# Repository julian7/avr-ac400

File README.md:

# Record Power AC400 controller

This repository contains a drop-in replacement PCB and firmware for the [Record Power AC400 Air Filter controller](https://www.recordpower.co.uk/product/two-stage-air-filter-with-remote-3-speeds-and-time-delay).

The original AC400 controller is prone to failure due to its simplistic power supply design, which often results in various failures. While the company's support is very good, the replacement controller is still prone to the same issues.

This design aims to provide a solution that is more robust, and tries to keep using original parts where possible. It also uses an ~~ATmega88PA~~ ATmega328P microcontroller, as existing refurbishment stock (note: the ATmega88 I had probably has SPIEN fuse unprogrammed, so I couldn't flash it at the end). The PCB and firmware is compatible with the whole line of ATmega48P/88P/168PA/328P line though.

## Case design

The board PCB is designed to fit into the original AC400 electronics enclosure, but there is a different LED divider grill design, which is 3D printed. The 3D model and the FreeCAD source are available in the `mechanical` directory, and it can be printed with a 3D printer.

The 3D design and model for the case is also provided, to allow further modifications.

## PCB design

The PCB is designed using KiCad 10, and is available in the `hardware` directory. The form factor is designed to fit into the original AC400 enclosure, and it uses the same connectors for the fan and power supply. It relies of the Alternative Kicad Library plugin for resistor footprints. Interactive BOM is generated using the [Interactive Html Bom](Github: https://github.com/openscopeproject/InteractiveHtmlBom) plugin, and gerber file packages are generated using the [gerber to order](https://github.com/asukiaaa/gerber_to_order) plugin.

## Firmware

The firmware is written in C using AVR-GCC toolchain, and it is available in the `firmware` directory. It is based on the original firmware functionality, with some improvements and bug fixes.

## Flashing the firmware

To flash the firmware onto the microcontroller, you will need an AVR programmer (e.g., USBasp, [ATMEL-ICE](https://www.microchip.com/en-us/development-tool/atatmel-ice)) and AVRDUDE software.

## Measurement points and troubleshooting

The PCB includes test points for measuring various signals:

- TP1: 3.3V power supply
- TP2: Ground
- TP3: Low speed mosfet drain
- TP4: Low speed mosfet gate
- TP5: Mid speed mosfet drain
- TP6: Mid speed mosfet gate
- TP7: High speed mosfet drain
- TP8: High speed mosfet gate

When troubleshooting, supply 3.3V power to the PCB through J8, so that 230V is not present on the board.

J1 is providing standard ISP connectivity. Manual reset can be performed by shorting JP1 (also labeled "RESET").

## Wiring and functions

When assembled into the original AC400 enclosure, the PCB will be connected to the following components:

- LINE IN: 230V AC input
- COMMON IN: Common line for the fan and the power supply
- COMMON OUT: White wire to the fan
- LOW OUT: Blue (or brown) wire to the fan
- MID OUT: Black wire to the fan
- HIGH OUT: Red wire to the fan

LED functions:

- LED1: Timer for 1 hour
- LED2: Timer for 2 hours
- LED3: Timer for 4 hours
- LED4: High speed indicator
- LED5: Medium speed indicator
- LED6: Low speed indicator

Button functions:

- SW1: On/Speed (cycles through Off, Low, Mid, High)
- SW2: Off

Infrared remote control functions:

- Red: Off
- Green: On/Speed
- Yellow: Timer (cycles through Off, 1 hour, 2 hours, 4 hours)

Buzzer signals:

- Short beep: Button press / infrared button feedback
- Long beep: Timer end
- Long beep with 1/2/4 short beeps: timer set to 1/2/4 hours
- Two long beeps: Off

## Build experience

Building this project was quite an experience. First off, soldering the MCU was not much of a challenge, and I felt like I could handle 0603 package size too, or even 0402 if the space is tight. I would use an ESP32-C3 board if I were to do it again: that would make it remote controllable.

Originally, I wanted to use an old ATmega88PA, but I couldn't even read its fuses. So that I ordered a few ATmega328P, which are pin-compatible. Fortunately, because I could made one of them a short circuit. It would've been nicer if the design accepted ATmega328PB, but I just didn't want to risk cutting wires at that point.

I almost fried my Raspberry Pi4 while writing the firmware, so buying a very cheap USBASP now feels like a no brainer. It's also not that bad if you don't screw up the ISP pinout. Fortunately, I could patch it up with bodge wires. Also, there was a nasty case of weird behavior and browning out, but as it turns out that was just microzig acting up. Switching back to avr-libc made the issue go away.

The original plan was to reuse the original case and the 12mm TACT switches, but I mistakenly ordered an earlier version of the PCB, where mounting holes have been placed closer together so I ended up 3D printing my own case. Later on, I even managed to break off the buttons as I tried to assemble it back together, and I only had 6x6mm switches so I ended up propping up some button spacers to be able to operate the device.

All in all, I'm very happy about the outcome.  Obviously it could've been much better, but this is still well beyond my expectations.

## Similar projects

- [AC400Controller](https://github.com/thikone/AC400Controller): drop-in replacement PCB, firmware, and 3D printed enclosure. It uses Arduino Nano as the controller.

## License

This project is licensed under the Creative Commons Attribution 4.0 International License. See the [LICENSE](./LICENSE.md) file for details.

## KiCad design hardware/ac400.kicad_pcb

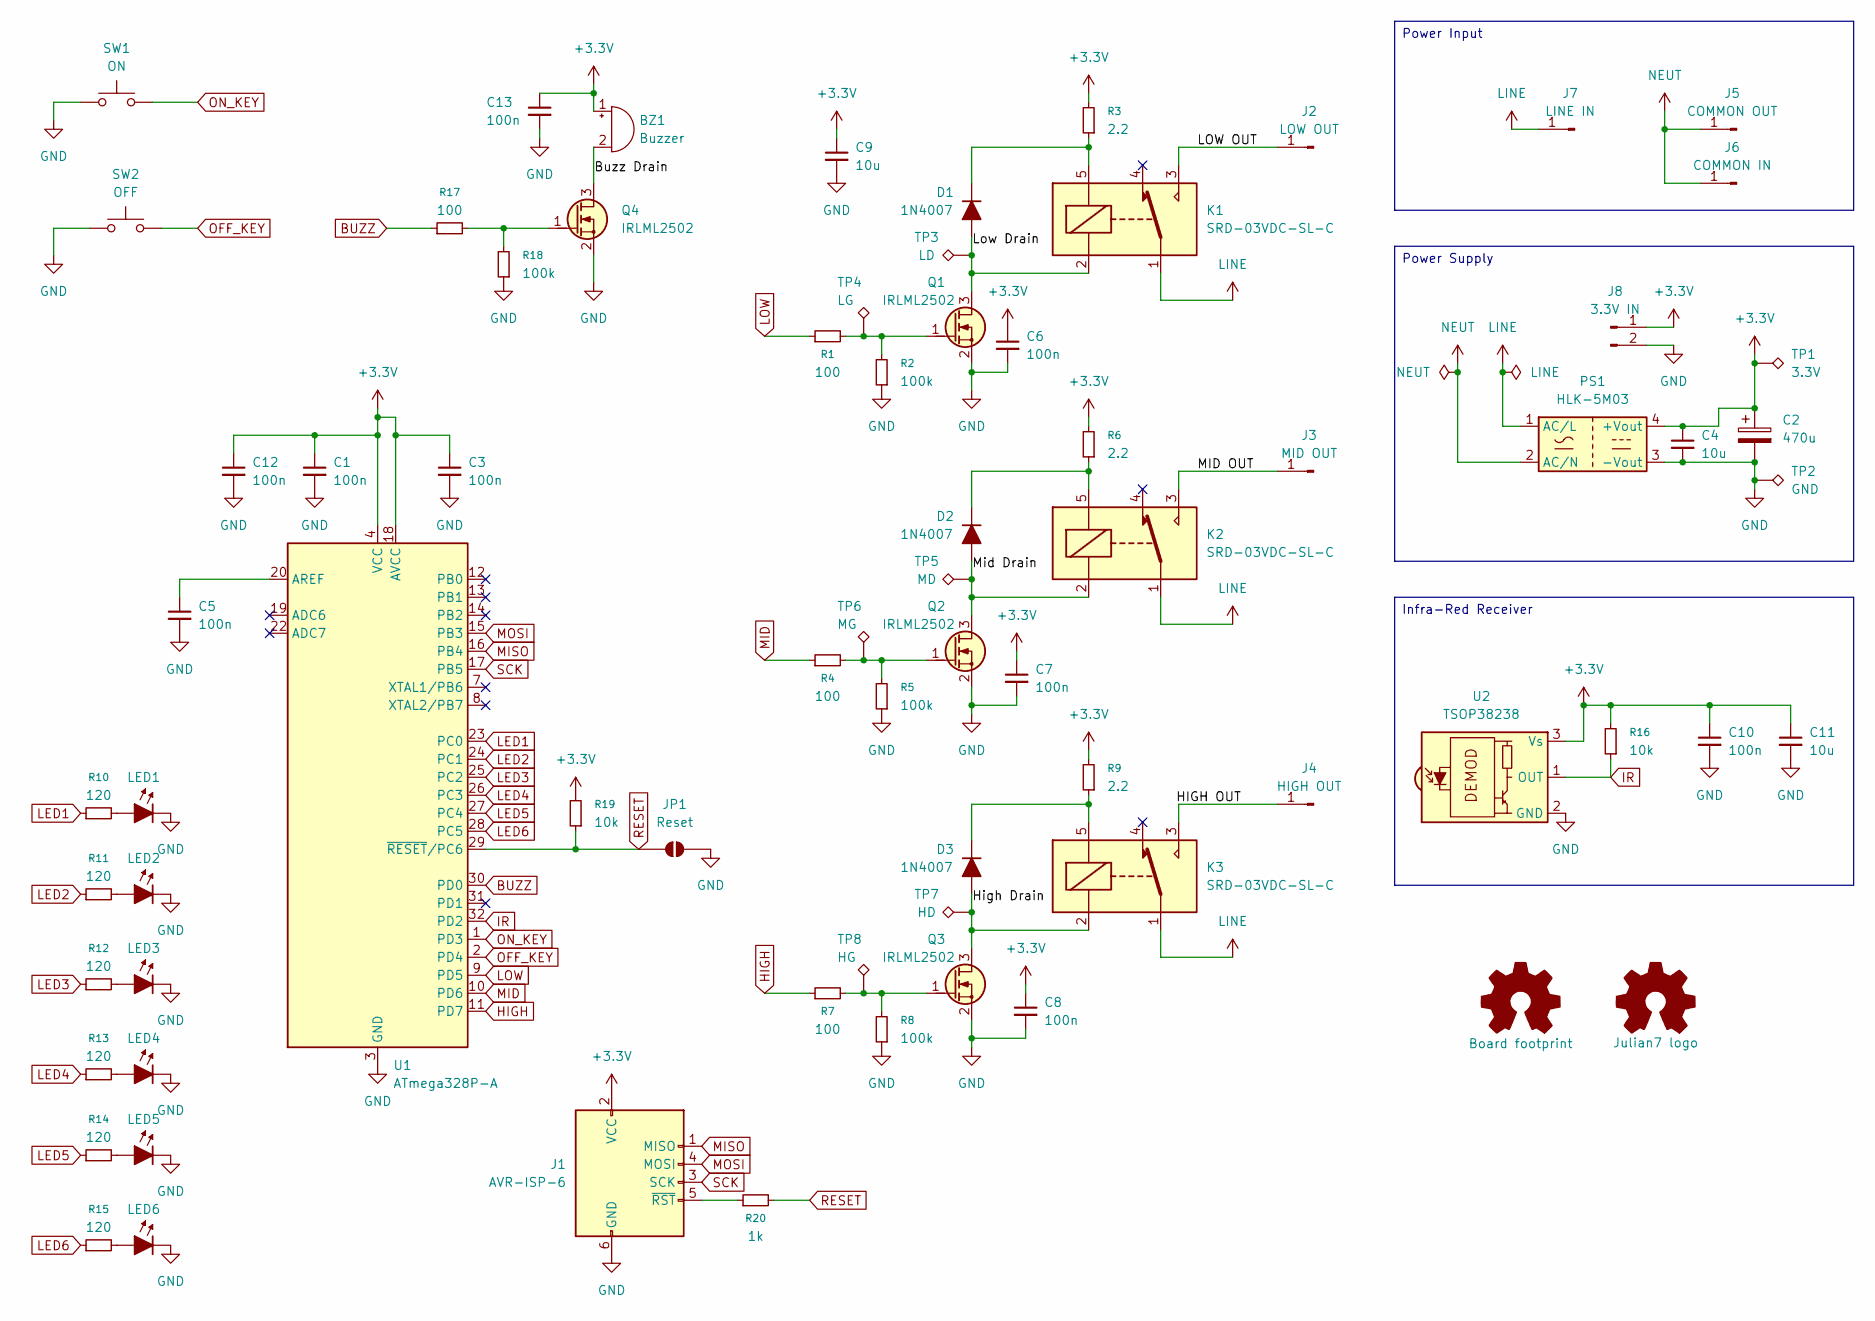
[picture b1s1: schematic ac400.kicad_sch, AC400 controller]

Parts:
BZ1: Buzzer; Buzzer_12x9.5RM7.6
C1, C3, C5, C6, C7, C8, C10, C12, C13: 100n; C_0805_2012Metric_Pad1.18x1.45mm_HandSolder
C2: 470u; CP_Radial_D8.0mm_P3.50mm
C4, C9, C11: 10u; C_0805_2012Metric_Pad1.18x1.45mm_HandSolder
D1, D2, D3: 1N4007; D_SOD-323
J1: AVR-ISP-6; IDC-Header_2x03_P2.54mm_Vertical
J2: LOW OUT; SolderWire-1.5sqmm_1x01_D1.7mm_OD3.9mm
J3: MID OUT; SolderWire-1.5sqmm_1x01_D1.7mm_OD3.9mm
J4: HIGH OUT; SolderWire-1.5sqmm_1x01_D1.7mm_OD3.9mm
J5: COMMON OUT; SolderWire-1.5sqmm_1x01_D1.7mm_OD3.9mm
J6: COMMON IN; SolderWire-1.5sqmm_1x01_D1.7mm_OD3.9mm
J7: LINE IN; SolderWire-1.5sqmm_1x01_D1.7mm_OD3.9mm
J8: 3.3V IN; PinHeader_1x02_P2.54mm_Vertical
JP1: Reset; SolderJumper-2_P1.3mm_Open_TrianglePad1.0x1.5mm
K1, K2, K3: SRD-03VDC-SL-C; Relay_SPDT_SANYOU_SRD_Series_Form_C
LED1, LED2, LED3, LED4, LED5, LED6: OF-SMD 2012 Green; LED_0805_2012Metric
PS1: HLK-5M03; Converter_ACDC_Hi-Link_HLK-5Mxx
Q1, Q2, Q3, Q4: IRLML2502; SOT-23
R1, R4, R7, R17: 100; R_0805_2012Metric_Pad1.15x1.40mm_HandSolder
R2, R5, R8, R18: 100k; R_0805_2012Metric_Pad1.15x1.40mm_HandSolder
R3, R6, R9: 2.2; R_0805_2012Metric_Pad1.15x1.40mm_HandSolder
R10, R11, R12, R13, R14, R15: 120; R_0805_2012Metric_Pad1.15x1.40mm_HandSolder
R16, R19: 10k; R_0805_2012Metric_Pad1.15x1.40mm_HandSolder
R20: 1k; R_0805_2012Metric_Pad1.15x1.40mm_HandSolder
SW1: ON; SW_PUSH-12mm
SW2: OFF; SW_PUSH-12mm
SYM1: Board footprint; board_shape
SYM2: Julian7 logo; julian7_makers_mark
TP1: 3.3V; TestPoint_Pad_D2.0mm
TP2: GND; TestPoint_Pad_2.0x2.0mm
TP3: LD; TestPoint_Pad_D2.0mm
TP4: LG; TestPoint_Pad_D2.0mm
TP5: MD; TestPoint_Pad_D2.0mm
TP6: MG; TestPoint_Pad_D2.0mm
TP7: HD; TestPoint_Pad_D2.0mm
TP8: HG; TestPoint_Pad_D2.0mm
U1: ATmega328P-A; TQFP-32_7x7mm_P0.8mm
U2: TSOP38238; Vishay_MINICAST-3Pin

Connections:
+3.3V: BZ1.1 (+), C1.1, C2.1, C3.1, C4.1, C6.1, C7.1, C8.1, C9.1, C10.1, C11.1, C12.1, C13.1, J1.2 (VCC), J8.1, PS1.4 (+Vout), R3.2, R6.2, R9.2, R16.2, R19.2, TP1.1 (1_1), U1.4 (VCC), U1.6 (VCC), U1.18 (AVCC), U2.3 (Vs)
/Buzz Drain: BZ1.2 (-), Q4.3 (D)
/HIGH OUT: J4.1 (Pin_1_1), K3.3
/High Drain: D3.2 (A), K3.2, Q3.3 (D), TP7.1 (1_1)
/LOW OUT: J2.1 (Pin_1_1), K1.3
/Low Drain: D1.2 (A), K1.2, Q1.3 (D), TP3.1 (1_1)
/MID OUT: J3.1 (Pin_1_1), K2.3
/Mid Drain: D2.2 (A), K2.2, Q2.3 (D), TP5.1 (1_1)
BUZZ: R17.1, U1.30 (PD0)
GND: C1.2, C2.2, C3.2, C4.2, C5.2, C6.2, C7.2, C8.2, C9.2, C10.2, C11.2, C12.2, C13.2, J1.6 (GND), J8.2, JP1.2 (B), LED1.1 (K), LED2.1 (K), LED3.1 (K), LED4.1 (K), LED5.1 (K), LED6.1 (K), PS1.3 (-Vout), Q1.2 (S), Q2.2 (S), Q3.2 (S), Q4.2 (S), R2.1, R5.1, R8.1, R18.1, SW1.1, SW2.1, TP2.1 (1_1), U1.3 (GND), U1.5 (GND), U1.21 (GND), U2.2 (GND)
HIGH: R7.1, U1.11 (PD7)
IR: R16.1, U1.32 (PD2), U2.1 (OUT)
LED1: R10.1, U1.23 (PC0)
LED2: R11.1, U1.24 (PC1)
LED3: R12.1, U1.25 (PC2)
LED4: R13.1, U1.26 (PC3)
LED5: R14.1, U1.27 (PC4)
LED6: R15.1, U1.28 (PC5)
LINE: J7.1 (Pin_1_1), K1.1, K2.1, K3.1, PS1.1 (AC/L)
LOW: R1.1, U1.9 (PD5)
MID: R4.1, U1.10 (PD6)
MISO: J1.1 (MISO), U1.16 (PB4)
MOSI: J1.4 (MOSI), U1.15 (PB3)
NEUT: J5.1 (Pin_1_1), J6.1 (Pin_1_1), PS1.2 (AC/N)
unnamed: D1.1 (K), K1.5, R3.1
unnamed: D2.1 (K), K2.5, R6.1
unnamed: D3.1 (K), K3.5, R9.1
unnamed: J1.5 (~RST), R20.1
unnamed: LED1.2 (A), R10.2
unnamed: LED2.2 (A), R11.2
unnamed: LED3.2 (A), R12.2
unnamed: LED4.2 (A), R13.2
unnamed: LED5.2 (A), R14.2
unnamed: LED6.2 (A), R15.2
unnamed: Q1.1 (G), R1.2, R2.2, TP4.1 (1_1)
unnamed: Q2.1 (G), R4.2, R5.2, TP6.1 (1_1)
unnamed: Q3.1 (G), R7.2, R8.2, TP8.1 (1_1)
unnamed: Q4.1 (G), R17.2, R18.2
unnamed: C5.1, U1.20 (AREF)
OFF_KEY: SW2.2, U1.2 (PD4)
ON_KEY: SW1.2, U1.1 (PD3)
RESET: JP1.1 (A), R19.1, R20.2, U1.29 (~RESET/PC6)
SCK: J1.3 (SCK), U1.17 (PB5)

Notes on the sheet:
Power Input
Power Supply
Infra-Red Receiver

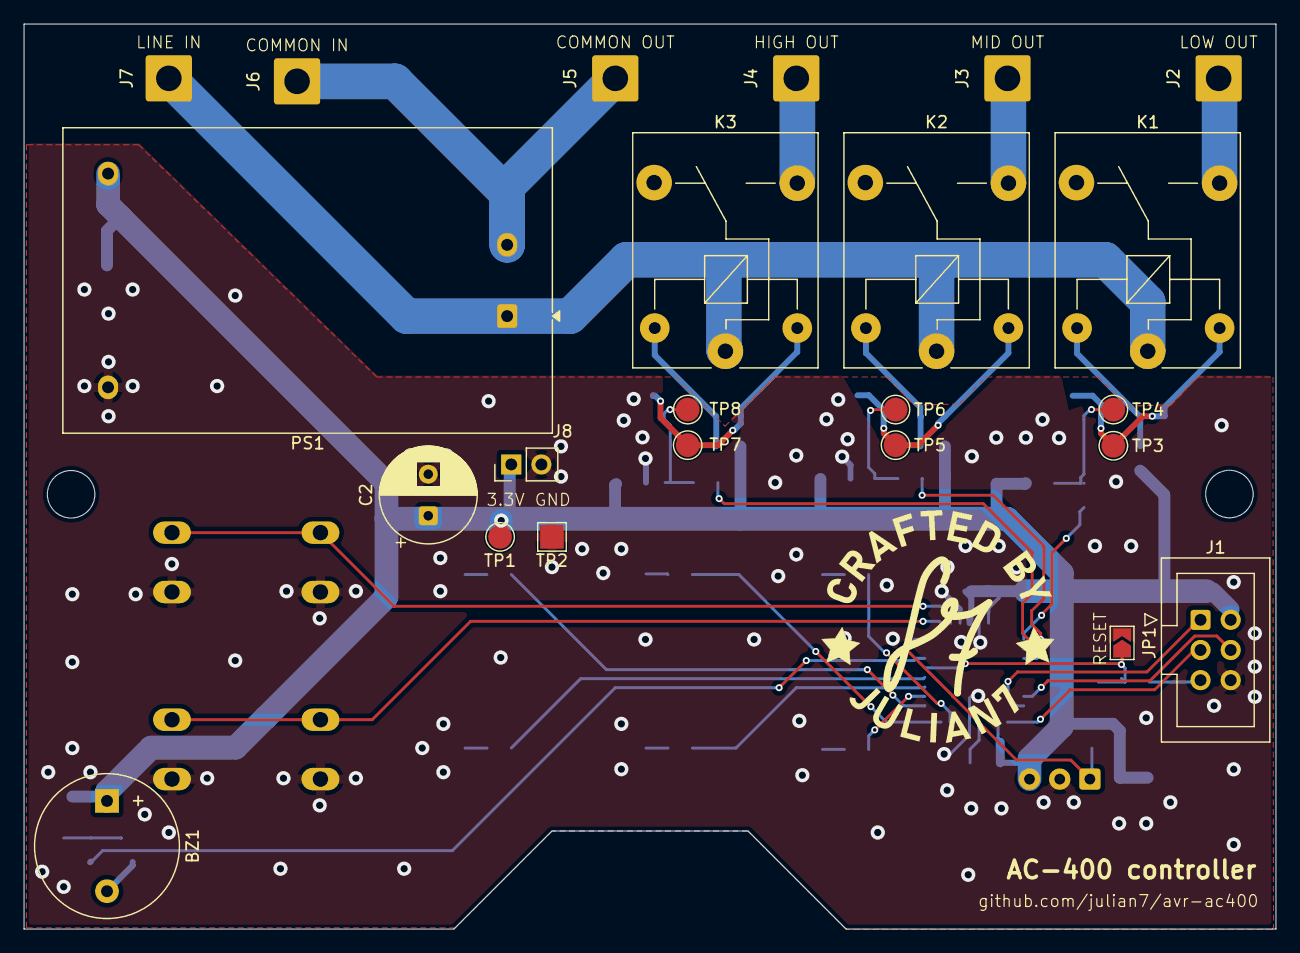
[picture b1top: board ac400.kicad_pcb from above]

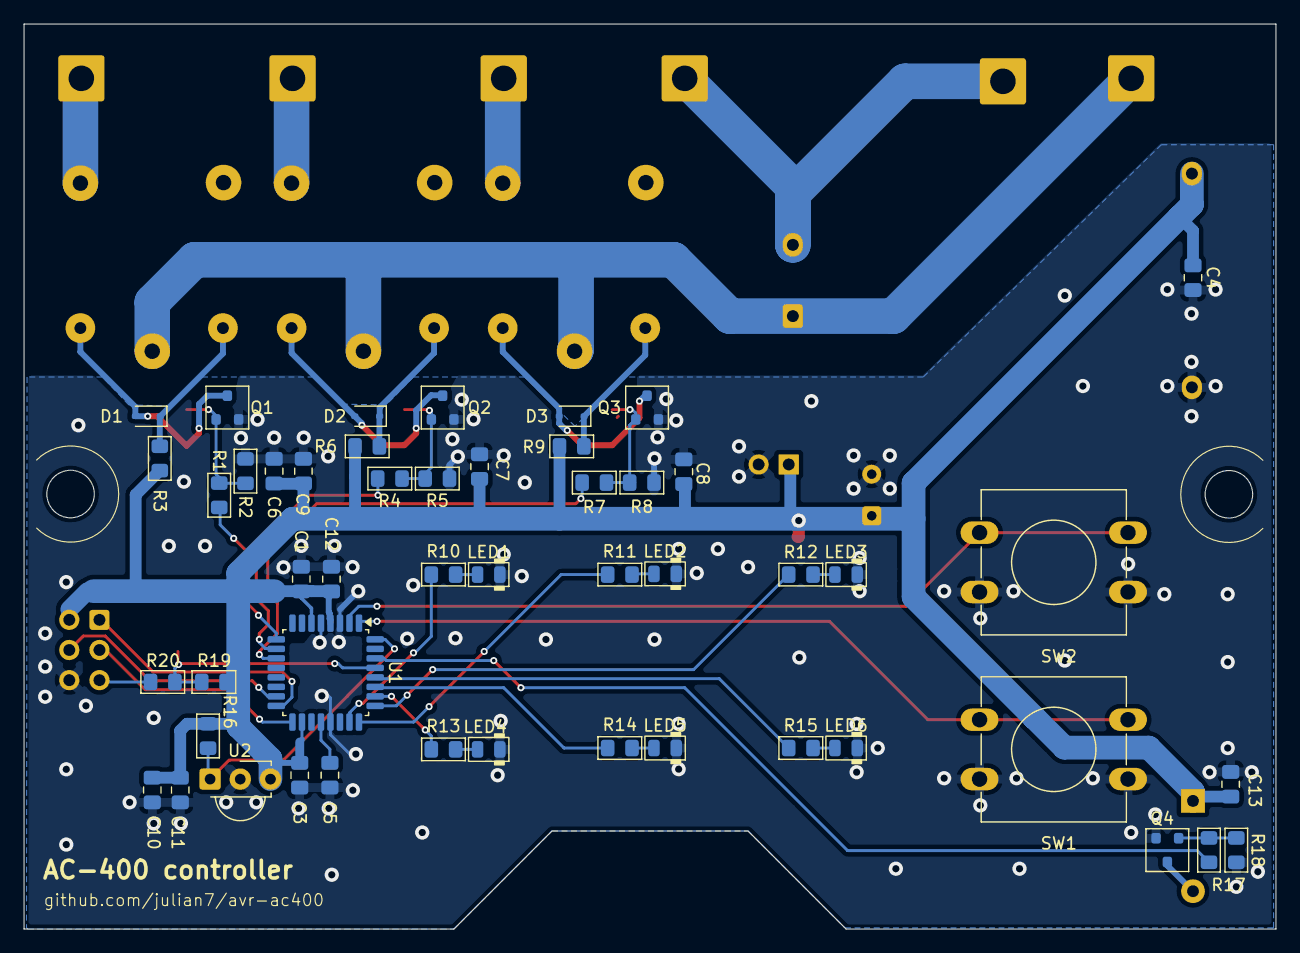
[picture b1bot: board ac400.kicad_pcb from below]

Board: 2 copper layers, 105.4 x 76.2 mm, 74 parts (49 on the bottom side), 43 nets.

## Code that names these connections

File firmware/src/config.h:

#ifndef CONFIG_H
#define CONFIG_H

#include "gpio.h"
#include <avr/io.h>
#include <stdint.h>

/*
 * Board configuration: signal mappings for ATmega328P
 *
 * - LEDs: PC0..PC5
 * - Buzzer: PD0
 * - IR: PD2 (INT0)
 * - Keys: PD3 (ON), PD4 (OFF)
 * - Relays: PD5 (LOW), PD6 (MID), PD7 (HIGH)
 */

#define LED1_PIN PIN_ENCODE(PORT_C, 0)
#define LED2_PIN PIN_ENCODE(PORT_C, 1)
#define LED3_PIN PIN_ENCODE(PORT_C, 2)
#define LED4_PIN PIN_ENCODE(PORT_C, 3)
#define LED5_PIN PIN_ENCODE(PORT_C, 4)
#define LED6_PIN PIN_ENCODE(PORT_C, 5)

#define BUZZER_PIN PIN_ENCODE(PORT_D, 0)
#define IR_PIN PIN_ENCODE(PORT_D, 2)
#define ON_KEY_PIN PIN_ENCODE(PORT_D, 3)
#define OFF_KEY_PIN PIN_ENCODE(PORT_D, 4)

#define RELAY_LOW_PIN PIN_ENCODE(PORT_D, 5)
#define RELAY_MID_PIN PIN_ENCODE(PORT_D, 6)
#define RELAY_HIGH_PIN PIN_ENCODE(PORT_D, 7)

#endif // CONFIG_H

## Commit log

2026-02-05 initial
2026-02-06 first swing at firmware
2026-02-06 link to the original product
2026-02-06 "final" touches on v1 board
2026-02-06 add license
2026-02-06 more docs
2026-02-08 mounting holes distance and library references fix
2026-02-08 LED divider grid
2026-02-19 generate / render files from kicad
2026-03-02 rewritten firmware in microzig
2026-03-05 Exclude non-component items from BOM
2026-03-07 Replace MCU, fix SPI pins and footprint
2026-03-07 update docs with schematic changes
2026-03-07 add box model, slightly shifted rail for divider
    rail had to be moved away, it wouldn't fit next to the switch.
2026-03-14 flashing is working
2026-03-22 fw is good, but IR has issues
2026-03-23 reimplement IR receiver
2026-03-23 more clarifications in README
2026-03-23 microzig firmware could never run
2026-03-23 update design to KiCad 10.0 version
2026-04-03 update kicad model to 10
2026-04-03 button shield and extender, better measurements
2026-04-03 update 3d models
